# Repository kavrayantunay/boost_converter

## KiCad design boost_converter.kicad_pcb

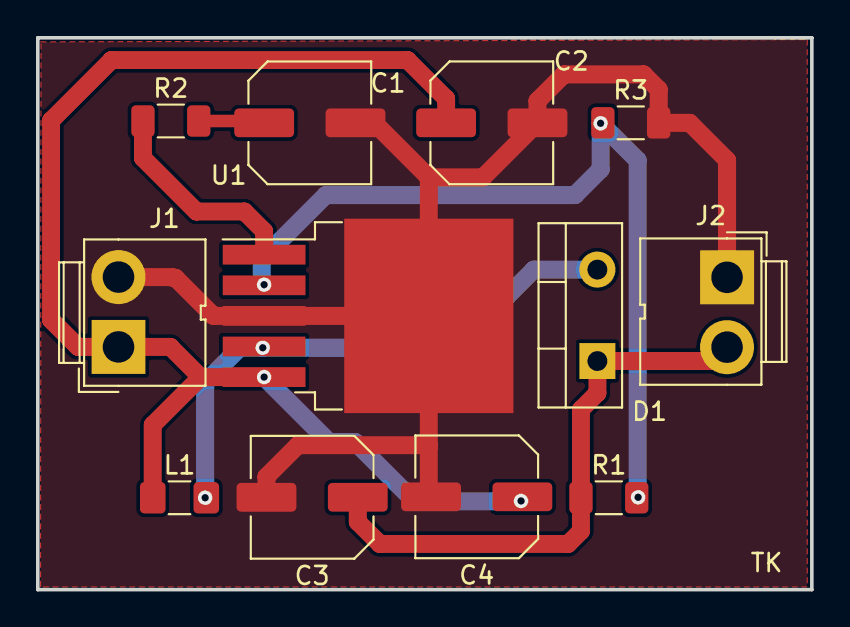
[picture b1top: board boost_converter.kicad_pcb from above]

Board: 2 copper layers, 43.0 x 30.7 mm, 12 parts (0 on the bottom side), 7 nets.

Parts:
C1: 1.5uF; C_Elec_6.3x5.8
C2: 56uF; C_Elec_6.3x5.8
C3: 1200uF; C_Elec_6.3x5.8
C4: 0.1uF; C_Elec_6.3x5.8
D1: BYV79-200; TO-220-2_Vertical
J1: IN; JWT_A3963_1x02_P3.96mm_Vertical
J2: OUT; JWT_A3963_1x02_P3.96mm_Vertical
L1: 150uH; L_1206_3216Metric_Pad1.42x1.75mm_HandSolder
R1: 75.7K; R_1206_3216Metric_Pad1.30x1.75mm_HandSolder
R2: 3K; R_1206_3216Metric_Pad1.30x1.75mm_HandSolder
R3: 2K; R_1206_3216Metric_Pad1.30x1.75mm_HandSolder
U1: LM2587; TO-263-5_TabPin3

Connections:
GND: C1.2, C2.2, C3.2, C4.2, J1.2 (GND), J2.1 (Vcc), R3.2, U1.3 (GND)
unnamed: C1.1, R2.2
unnamed: C2.1, C4.1, J1.1 (Vcc), L1.1, U1.5 (VIN)
unnamed: C3.1, D1.1 (K), J2.2 (GND), R1.1
unnamed: D1.2 (A), L1.2, U1.4 (SWTCH)
unnamed: R1.2, R3.1, U1.2 (FB)
unnamed: R2.1, U1.1 (COMP)
